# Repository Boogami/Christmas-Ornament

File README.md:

# Christmas Ornament 2020

# Description

This is a Christmas ornament specifically done for 2020. A year to be remembered.

Merry Christmas!! :santa: :christmas_tree: :gift:

---

# Tools

- Inkscape
- svgtoeagle https://gfwilliams.github.io/svgtoeagle/
- Eagle
- Fusion 360

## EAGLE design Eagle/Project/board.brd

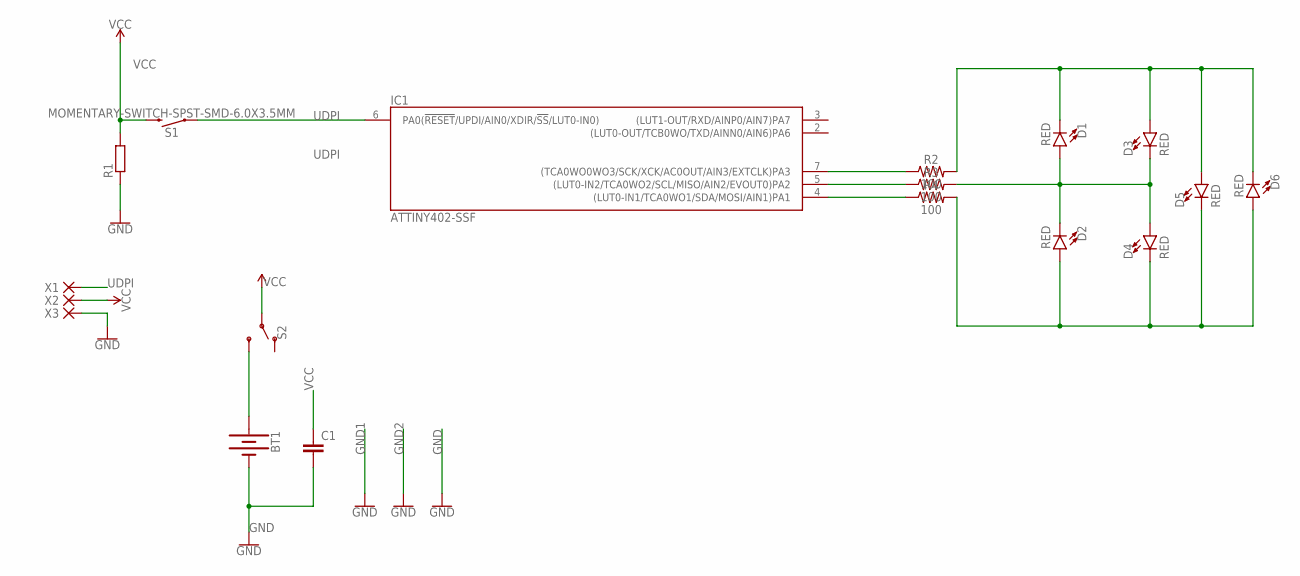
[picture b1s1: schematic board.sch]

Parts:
BT1: BATTERY-20MM_SMD; BATTCON_20MM
C1: C-EUC0805; C0805
D1, D2, D3, D4, D5, D6: RED; LED-0603
IC1: ATTINY402-SSF; SO8
R1: R-EU_R0603; R0603
R2, R3, R4: 100; 0603
S1: MOMENTARY-SWITCH-SPST-SMD-6.0X3.5MM; TACTILE_SWITCH_SMD_6.0X3.5MM
S2: SWITCH-SPDT-SMD-RIGHT-ANGLE; SWITCH_SPST_SMD_A
X1, X2, X3: PAD-1.27X2.54

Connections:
GND: BT1.2 (-), C1.2, IC1.8 (GND), R1.1, X3.1
unnamed: D1.C, D3.A, D5.A, D6.C, R2.2
unnamed: IC1.7 ((TCA0WO0WO3/SCK/XCK/AC0OUT/AIN3/EXTCLK)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), R2.1
unnamed: IC1.5 ((LUT0-IN2/TCA0WO2/SCL/MISO/AIN2/EVOUT0)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), R3.1
unnamed: IC1.4 ((LUT0-IN1/TCA0WO1/SDA/MOSI/AIN1)PA1), R4.1
unnamed: D2.A, D4.C, D5.C, D6.A, R4.2
unnamed: BT1.1 (+), S2.3 (S)
unnamed: D1.A, D2.C, D3.C, D4.A, R3.2
UDPI: IC1.6 (PA0(!RESET!/UPDI/AIN0/XDIR/!SS!/LUT0-IN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), S1.1, X1.1
VCC: C1.1, IC1.1 (VCC), R1.2, S1.2, S2.2, X2.1

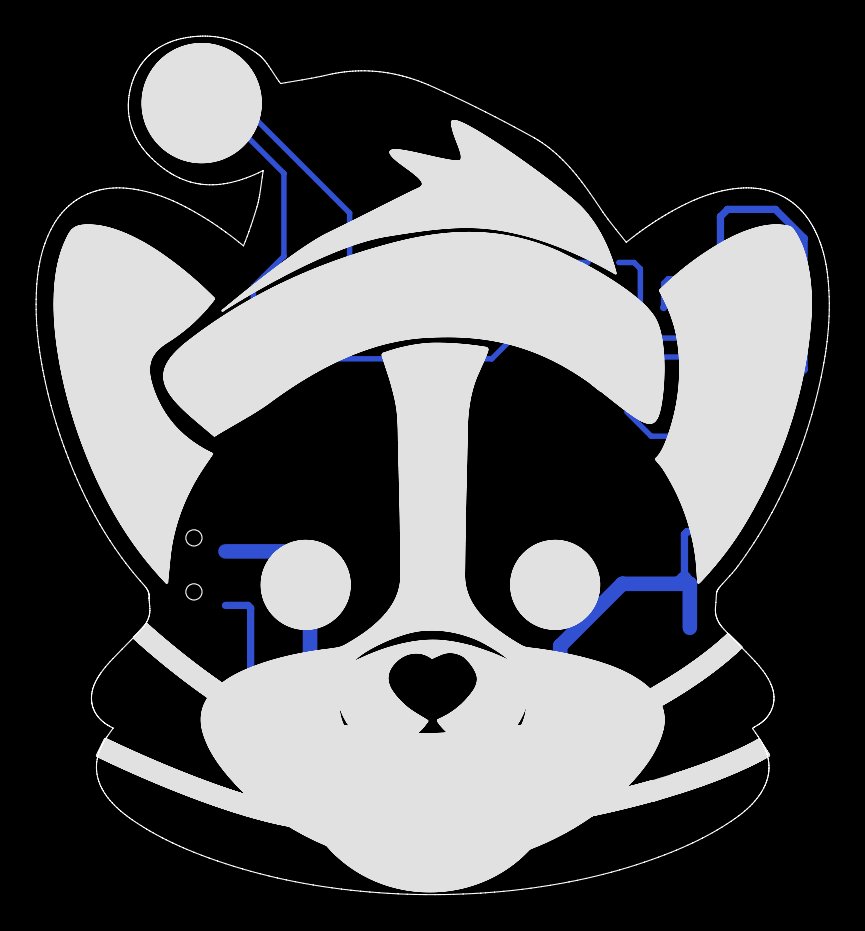
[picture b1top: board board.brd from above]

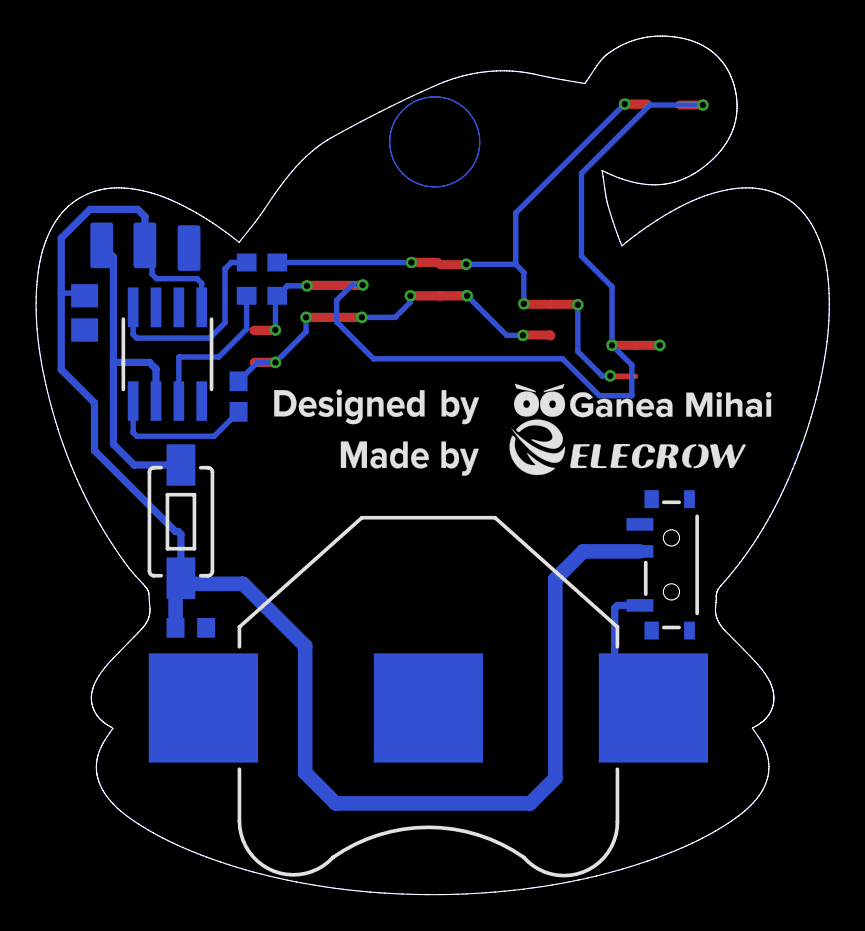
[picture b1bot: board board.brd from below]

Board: 2 copper layers, 44.1 x 47.7 mm, 18 parts (12 on the bottom side), 10 nets.

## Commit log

2020-12-12 Updated project
2020-12-12 Added gerber files
2020-12-12 Changed gerber file

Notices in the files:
parts and their libraries:
SparkFun-LED: Licensing: Creative Commons ShareAlike 4.0 International - https://creativecommons.org/licenses/by-sa/4.0
